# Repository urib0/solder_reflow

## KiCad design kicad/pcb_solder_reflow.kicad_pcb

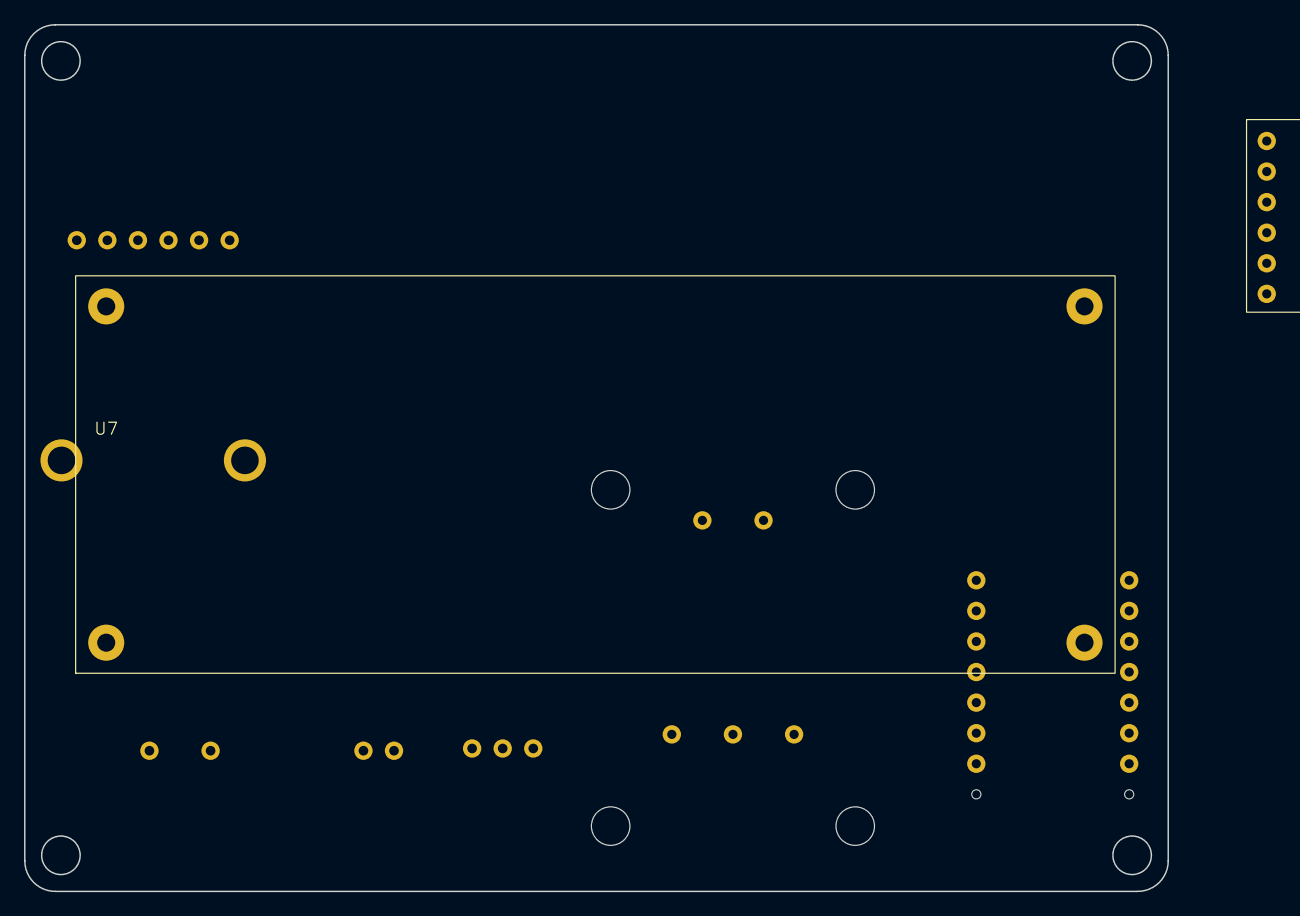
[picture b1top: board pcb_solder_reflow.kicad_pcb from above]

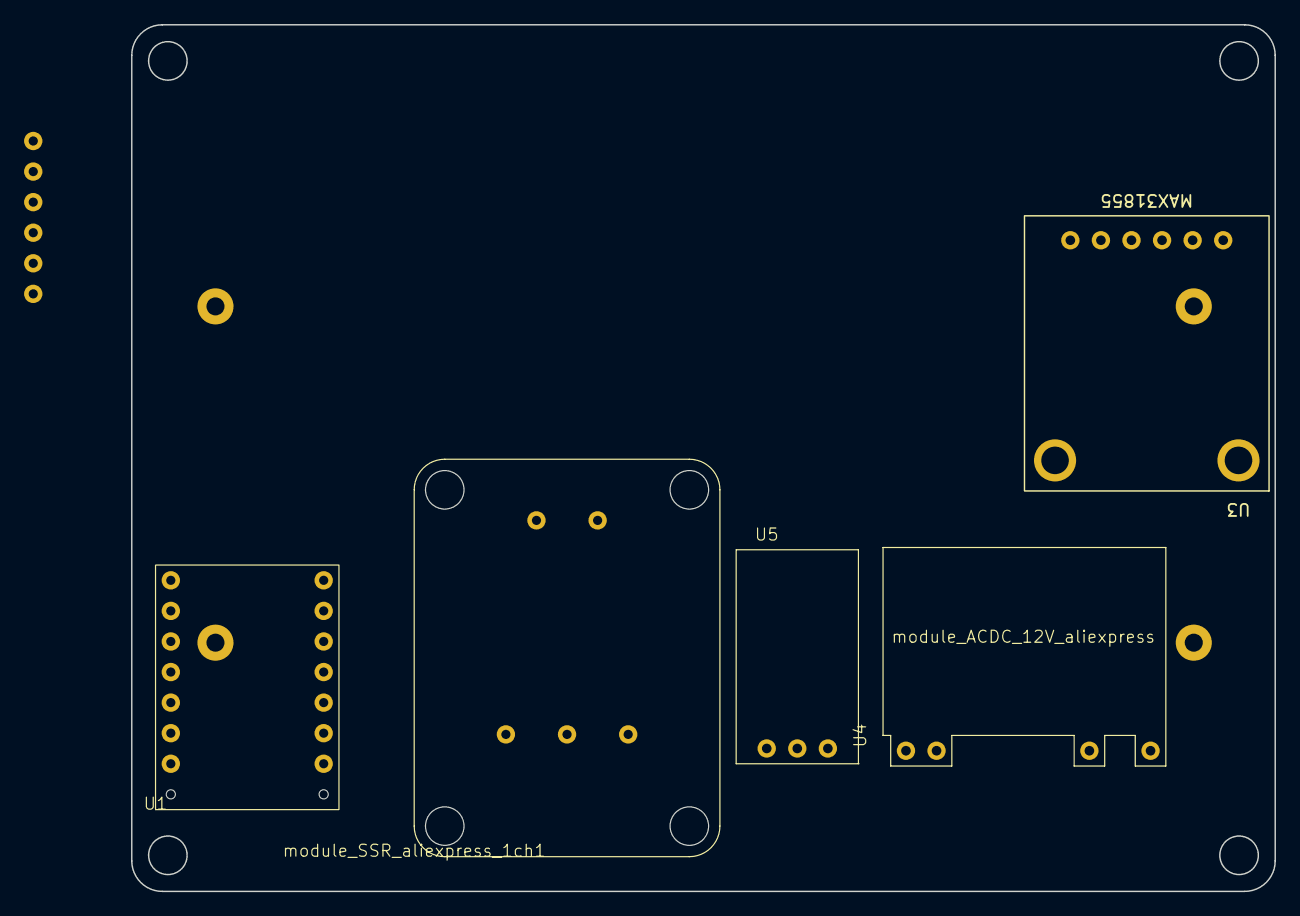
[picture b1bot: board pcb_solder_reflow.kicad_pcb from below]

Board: 2 copper layers, 95.0 x 72.0 mm, 7 parts (5 on the bottom side), 10 nets, no tracks yet.

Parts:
U1: ATTINYx14; module_ATTINYxxx4
U2: module_CH340E
U3: module_ADA_MAX31855
U4: module_ACDC_12V_aliexpress
U5: module_DCDC_5V_aliexpress; module_DCDC_12V_aliexpress
U7: module_LCD_I2C; module_LCD_1602_I2C_aliexpress
module_SSR_aliexpress_1ch1: module_SSR_aliexpress_1ch_0_1

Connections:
+5V: U1.1 (VCC), U2.2 (5V), U3.1 (Vin), U5.3 (Vout), module_SSR_aliexpress_1ch1.1 (DC+)
+12V: U4.3 (V+), U5.1 (Vin)
AC/N: U4.2 (AC/N), module_SSR_aliexpress_1ch1.5 (SW_B)
CLK: U1.11 (MOSI/PA1), U3.6 (CLK)
CS: U1.12 (MISO/PA2), U3.5 (CS)
DO: U1.13 (SCK/PA3), U3.4 (DO)
GND: U1.14 (GND), U2.1 (GND), U3.3 (GND), U4.4 (V-), U5.2 (GND), module_SSR_aliexpress_1ch1.2 (DC-)
RXD: U1.7 (PB2/TXD), U2.4 (RXD)
SSR: U1.10 (UPDI/PA0), module_SSR_aliexpress_1ch1.3 (CH1)
TXD: U1.6 (PB3/RXD), U2.3 (TXD)
